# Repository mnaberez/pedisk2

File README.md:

# PEDISK II

This repository holds reverse engineering work on the
[PEDISK II](http://mikenaberezny.com/hardware/pet-cbm/microtech-pedisk-ii/) from CGRS Microtech,
a floppy disk controller for Commodore PET/CBM computers.

## Files

 - `rom_e800.bin` is a binary dump of the EPROM.

 - `rom_e800.asm` is a disassembly of it.

## Assemble

The `.asm` files can be assembled with the
[ACME](http://www.esw-heim.tu-clausthal.de/~marco/smorbrod/acme/)
assembler:

    $ acme -v1 --outfile test.bin pedisk2.asm

It should assemble a binary that is identical to the original.

## Credits

- Lee Davison did the initial disassembly of the ROM.
- Jim Oldfield provided the 5.25" PEDISK disks from which the DOS code was
  recovered.
- Mike Naberezny disassembled the 5.25" DOS code, adapted it for 8", and wrote
  the image tools.
- Steve Hirsch provided help and formatted 8" disks used for early testing.
- Josh Bensadon reverse engineered the original PCB and made the schematic.
- Steve Gray made the replica PCB layout and had boards manufactured.
- Mike Stein built the replica and provided help and input throughout.
- Bill Goble, the original designer of the PEDISK, found and donated the
  original manuals, schematics, source code, and master disks.

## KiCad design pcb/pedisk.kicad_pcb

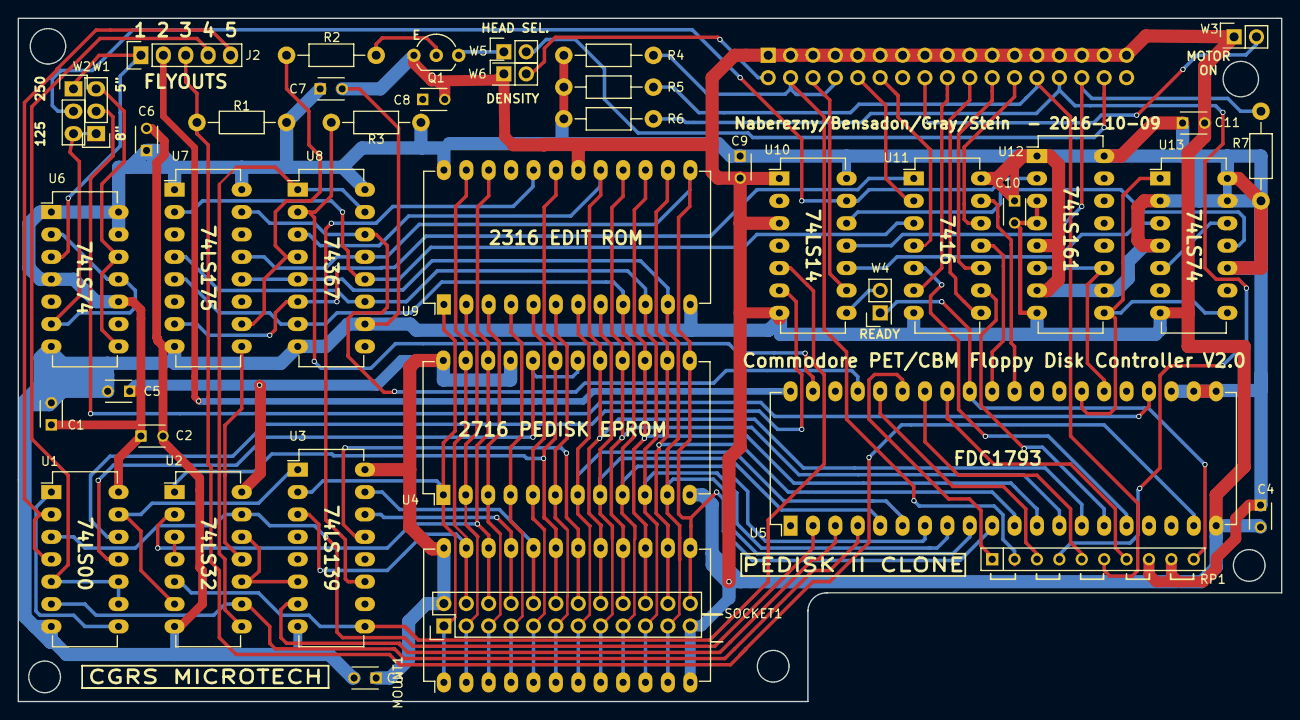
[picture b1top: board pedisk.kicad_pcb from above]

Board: 2 copper layers, 143.3 x 77.5 mm, 43 parts (1 on the bottom side), 82 nets.

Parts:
C1, C2, C3, C4, C5, C6, C7, C8, C9, C10, C11: C; C_Disc_D3_P2.5
J2: CONN_01X05; Pin_Header_Straight_1x05
MOUNT1: 2316; DIP-24_W15.24mm_LongPads
P1: CONN_02X17; IDC_Header_Straight_34pins
Q1: 2N2222; TO-92_Inline_Wide
R1, R2, R3, R7: 3.3K; Resistor_Horizontal_RM10mm
R4, R5, R6: 150ohm; Resistor_Horizontal_RM10mm
RP1: 4.7K; Resistor_Array_SIP9
SOCKET1: CONN_02X12; Pin_Header_Straight_2x12
U1: 74HC00; DIP-14_W7.62mm_LongPads
U2: 74LS32; DIP-14_W7.62mm_LongPads
U3: 74LS139; DIP-16_W7.62mm_LongPads
U4: 2716; DIP-24_W15.24mm_LongPads
U5: FD1793; DIP-40_W15.24mm_LongPads
U6, U13: 74LS74; DIP-14_W7.62mm_LongPads
U7: 74LS175; DIP-16_W7.62mm_LongPads
U8: 74LS367; DIP-16_W7.62mm_LongPads
U9: 2316; DIP-24_W15.24mm_LongPads
U10: 74HC14; DIP-14_W7.62mm_LongPads
U11: 74LS05; DIP-14_W7.62mm_LongPads
U12: 74LS161; DIP-16_W7.62mm_LongPads
W1: 8 5; Pin_Header_Straight_1x03
W2: 250 125; Pin_Header_Straight_1x03
W3, W4, W5, W6: CONN_02X01; Pin_Header_Straight_2x01

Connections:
5V: C1.1, C2.1, C3.1, C4.1, C5.1, C6.1, C7.1, C8.1, C9.1, C10.1, C11.1, MOUNT1.24, R1.2, R3.1, R4.1, R5.1, R6.1, R7.1, RP1.8, RP1.9, SOCKET1.2, U1.14, U2.14, U3.16, U4.21, U4.24, U5.21, U5.22, U5.23, U6.1, U6.4, U6.10, U6.13, U6.14, U7.1, U7.16, U8.16, U9.21, U9.24, U10.14, U11.14, U12.1, U12.5, U12.7, U12.10, U12.16, U13.2, U13.4, U13.10, U13.13, U13.14
12VOLTS: J2.2, U5.40
A0: MOUNT1.8, SOCKET1.15, U4.8, U5.5, U9.8
A1: MOUNT1.7, SOCKET1.13, U4.7, U5.6, U9.7
A2: MOUNT1.6, SOCKET1.11, U4.6, U9.6
A3: MOUNT1.5, SOCKET1.9, U4.5, U9.5
A4: MOUNT1.4, SOCKET1.7, U4.4, U9.4
A5: MOUNT1.3, SOCKET1.5, U4.3, U9.3
A6: MOUNT1.2, SOCKET1.3, U4.2, U9.2
A7: MOUNT1.1, SOCKET1.1, U3.2, U4.1, U9.1
A8: MOUNT1.23, SOCKET1.4, U3.3, U4.23, U9.23
A9: MOUNT1.22, SOCKET1.6, U2.2, U4.22, U9.22
A10: MOUNT1.19, SOCKET1.12, U2.1, U4.19, U9.19
A11: MOUNT1.21, SOCKET1.8, U3.14
CLK: U5.24, W1.2
CLOCK: J2.1, U6.3, W2.1
D0: MOUNT1.9, SOCKET1.17, U4.9, U5.7, U7.5, U8.7, U9.9
D1: MOUNT1.10, SOCKET1.19, U4.10, U5.8, U7.4, U8.11, U9.10
D2: MOUNT1.11, SOCKET1.21, U4.11, U5.9, U7.12, U8.5, U9.11
D3: MOUNT1.13, SOCKET1.24, U4.13, U5.10, U7.13, U8.13, U9.13
D4: MOUNT1.14, SOCKET1.22, U4.14, U5.11, U9.14
D5: MOUNT1.15, SOCKET1.20, U4.15, U5.12, U9.15
D6: MOUNT1.16, SOCKET1.18, U4.16, U5.13, U9.16
D7: MOUNT1.17, SOCKET1.16, U4.17, U5.14, U8.3, U9.17
DENSITY: P1.2, W6.2
DIRC: P1.18, U11.6
E: J2.5, U1.2, U1.4
EPROM_CS: U1.11, U4.18, U4.20
FDC_CS: U3.7, U5.3
FDC_RE: U1.6, U2.9, U5.4
FDC_WE: U1.3, U2.13, U5.2
GND: C1.2, C2.2, C3.2, C4.2, C5.2, C6.2, C7.2, C8.2, C9.2, C10.2, C11.2, MOUNT1.12, P1.1, P1.3, P1.5, P1.7, P1.9, P1.11, P1.13, P1.15, P1.17, P1.19, P1.21, P1.23, P1.25, P1.27, P1.29, P1.31, P1.33, Q1.1, SOCKET1.23, U1.7, U2.7, U3.8, U4.12, U5.20, U6.7, U7.8, U8.8, U8.10, U9.12, U9.18, U10.1, U10.3, U10.7, U11.7, U12.3, U12.4, U12.8, U13.7, W3.1, W6.1
HDSEL: P1.32, W5.2
INDEX: P1.4, P1.8, R4.2, RP1.2
INTRQ: R3.2, U5.39, U8.2
LATCH_READ: U2.8, U8.1, U8.15
LATCH_WRITE: U2.11, U7.9
MOTOR: P1.16, W3.2
unnamed: Q1.2, R2.2
unnamed: Q1.3, W5.1
unnamed: R2.1, U7.10, U8.4
unnamed: RP1.1, U5.35
unnamed: RP1.3, U5.36
unnamed: RP1.5, U5.34
unnamed: RP1.7, U5.33
unnamed: RP1.10, U5.32, W4.1
unnamed: U1.1, U1.8
unnamed: U1.12, U10.6
unnamed: U1.13, U2.6, U3.1
unnamed: U2.3, U2.4
unnamed: U2.10, U2.12, U3.6
unnamed: U6.2, U6.6, U6.11, W1.1, W2.3
unnamed: U6.8, U6.12, W1.3
unnamed: U2.5, U3.9, U10.5
unnamed: U10.8, W4.2
unnamed: U10.10, U13.3
unnamed: U10.12, U13.11
unnamed: U10.13, U12.2, W2.2
unnamed: U7.7, U8.6, U11.1
unnamed: U7.2, U8.12, U11.3
unnamed: U5.16, U11.5
unnamed: U5.15, U11.9
unnamed: U5.31, U11.11
unnamed: U5.30, U11.13
unnamed: U13.5, U13.12
R/~W: J2.4, U1.5, U1.9, U1.10
RAWREAD: U5.27, U12.9, U13.1, U13.8
RCLK: U5.26, U12.6, U12.11
RDATA: P1.30, R7.2, U10.11
READY: P1.6, U10.9
RESET: J2.3, R1.1, U5.19
ROM_CS: U3.11, U9.20
SEL1: P1.10, U11.2
SEL2: P1.12, U11.4
SOCKET_CS: MOUNT1.20, SOCKET1.10, U3.15
SOCKET_OE: MOUNT1.18, SOCKET1.14, U3.13
STEP: P1.20, U11.8
TRK00: P1.26, R5.2, RP1.6
WDAT: P1.22, U11.10
WGATE: P1.24, U11.12
WPROT: P1.28, R6.2, RP1.4
~DDEN: U5.37, U7.15, U8.14

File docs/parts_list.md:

Parts List
----------

| Reference      | Part               |
|----------------|--------------------|
| C1-11          | 0.1 uF             |
| J1             | 34-pin Header      |
| Q1             | 2N2222 (??)        |
| R1, R2, R3, R7 | 3.3 K              |
| R4, R5, R6     | 150 Ohm            |
| RN1            | 4.7 K              |
| U1             | 74LS00             |
| U2             | 74LS32             |
| U3             | 74LS139            |
| U4             | 2716               |
| U5             | WD1793             |
| U6             | 74LS74             |
| U7             | 74LS175            |
| U8             | 74367              |
| U9             | 901474-03          |
| U10            | 74LS14             |
| U11            | 7416               |
| U12            | 74LS161            |
| U13            | 74LS74             |
| W1, W2         | 3-pin Jumper Block |
| W3, W4, W5     | 2-pin Jumper Block |

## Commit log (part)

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2015-02-21 Fix disassembly of JSR $7818
2015-02-21 Add labels for menu commands
2015-02-21 Add label l_ead1 for $EAD1
2015-02-21 Replace $7FB1 with drive_sel_f
2015-02-21 Found filler area
2015-02-21 Add labels and comments to internal commands
2015-02-21 Add label try_extrnl_cmd for $7a47
2015-02-21 Found hex word input
2015-02-21 Found character input
2015-02-22 Replace LB8F6 with linget
2015-02-22 Remove unused equates
2015-02-22 Replace $7a47 with try_extrnl_cmd
2015-02-22 Use character literal for command "P"
2015-02-22 Remove unused equate
2015-02-22 Replace L7AD1 with input_device
2015-02-22 Use equates for filename and drive_sel_f
2015-02-22 Replace $7ee0 with buf_4
2015-02-22 Move original binaries to bin/
2015-02-22 Found pointers to dir_sector
2015-02-22 Use equates for track, sector, drive_sel
2015-02-22 Replace $26 with hex_save_a
2015-02-22 Replace $22/23 with dir_ptr
2015-02-22 Add equates for RAM locations, add comments to program flow
2015-02-22 Replace $ea2f with drive_selects
2015-02-22 Use equate for chrin
2015-02-22 Replace $e900 with latch
2015-02-23 Add note that BASIC shortcuts can be used
2015-02-23 Fix indentation
2015-02-23 Add comments to menu input
2015-02-23 Replace $7800 with dos_stop
2015-02-23 Replace $7fe0 with wedge_stack
2015-02-23 Found tokenized BASIC at $7d0c
2015-02-23 Found tokenized BASIC at $7a00
2015-02-23 Add error info for select_drive, seek_track, find_file, load_file
2015-02-24 Add comments to find_file and load_file error handling
2015-02-24 Add comments to load program and execute program
2015-02-24 Rename exec_file to exec_prog for consistency
2015-02-24 Found start and entry addresses
2015-02-24 Replace $11/12 with linnum
2015-02-24 Add comments with directory entry indexes
2015-02-24 Found routine that prints filename
2015-02-24 Rename dir_a/dir_b to old_dir/new_dir
2015-02-24 Fix description of used file entry count
2015-02-24 Add labels and comments to directory manipulation
2015-02-25 Add equate tmp_7f97 for $7f97
2015-02-25 Found file data buffer
2015-02-25 Found number of used entries and next open track/sector
2015-02-25 Found directory read and write
2015-02-25 Found start of file move
2015-02-25 Add equate tmp_7f9a for $7f9a
2015-02-25 Add comments to sector increment error handling
2015-02-25 Rename start_move_file to move_file_loop
2015-02-25 Add equate intflg for $08
2015-02-25 Found 16 byte buffer for directory entry
2015-02-25 Remove equate L0076
2015-02-25 Add comments to explain dir_entry offsets
2015-02-25 Rename l_ead1 to restart_dos
2015-02-26 Add description of disk error message
2015-02-26 Found possible sectors per track constant
2015-02-26 Found file exists error code
2015-02-26 Add note about drive selection in seek_track
2015-02-26 Found return values for wait_for_fdc and wait_fdc_status
2015-02-27 Add comments to directory initialization
2015-02-27 Fix description of drive select
2015-02-27 Start format program to bootstrap a PEDISK disk
2015-02-28 Formats a disk successfully
2015-02-28 Fix description of track seek
2015-02-28 Print "FORMAT TRACK" before each track, not after
2015-02-28 Write empty directory after format
2015-03-01 Add comments to kill_file
2015-03-01 Add comments to input_device, rename L7ADB to parse_drive
2015-03-01 Fix typo
2015-03-02 Found BASIC tokens in _dos_run
2015-03-02 Add note about unused bytes in directory header
2015-03-02 Rename L7DDB to wait_for_r_key
2015-03-02 Remove unused label L7CAE
2015-03-02 Found source and destination drives
2015-03-02 Found sector buffer at $7e00
2015-03-02 Found buffer used to store sectors during copy
2015-03-02 Found current track number during copy
2015-03-02 Remove unused label hit_r_key
2015-03-03 Replace $7b59 with L7B59
2015-03-06 Clarify that head load solenoid may not only be 8"
2015-03-06 Rename deselect to deselect_drive for parity with select_drive
2015-03-07 Found save routine
2015-03-09 Add note with file types that can be loaded
2015-03-12 Assemble format.asm on Travis
2015-03-13 Found "restore" command
2015-03-23 Found purpose of status check after write protect check
2015-03-28 Add TODO for offset $0b in directory entry
2015-04-03 Add troubleshooting note about double sided disks
2015-04-04 Add troubleshooting note about hard sectored disks
2015-04-05 Fix typo in string
2015-04-06 Found usage for !OPEN, !CLOSE, !PRINT, !INPUT Issue 2 of the PEDISK newsletter has a program listing that shows these commands in use.
2015-04-06 Found optional keywords that may follow !OPEN
2015-04-06 Found another possible BASIC token
2015-04-06 Use character literal for colon
2015-04-07 Found basics of record handling for !PRINT and !INPUT
2015-04-07 Found record count specifier
2015-04-08 Found unknown END mode of !OPEN
2015-04-08 Found strings
2015-04-08 Found error codes set in FC% variable
2015-04-08 Found error handler for sequential commands
2015-04-10 Found FC% error codes for !OPEN
2015-04-12 Found routine to get open file number
2015-04-12 Found error code for file not open
2015-04-12 Found error code for too many open files
2015-04-12 Found !OPEN logic for create new or open existing
2015-04-12 Add labels to !OPEN routines
2015-04-12 Rename L7B2F to file_num_to_xy
2015-04-13 Replace $7BE9 with label
2015-04-13 Found error code for position out of range
2015-04-14 Fix usage of POS keyword
2015-04-14 Found FC% error code for OK
2015-04-14 Rename L79F3 to sys_disk_err
2015-04-16 Rename L7BA6 to handle_filename
2015-04-16 Remove unused label
2015-04-16 Add labels for open_create branches
2015-04-18 Found filler bytes at $79f6
2015-04-20 Remove old TODO
2015-04-21 Remove old reference to buf_*
2015-04-22 Add note with L7931 callers
2015-04-23 Add description of input_filename
2015-04-25 Remove incorrect comment
2015-04-25 Rename l_ed38 to cli_rts
2015-04-26 Rename L7D7D to "done"
2015-04-26 Compact filler area
2015-05-08 Use sector_size constant
2015-05-11 Remove comment
2015-11-16 Add class for manipulating PEDISK image data
2015-11-16 Fix empty space fill byte
2015-11-16 Move format into Filesystem object
2015-11-16 Add tests for format
2015-11-16 Pad diskname to 8 bytes
2015-11-16 Add method to find next available track/sector
2015-11-16 Add properties to find free space
2015-11-16 Add method to write an LD file
2015-11-16 Fix missing entry address
2015-11-17 Add a script to make a boot disk
2015-11-17 Add description for format program
2015-11-17 Add bootstrap file generator
2015-11-17 Display code if error occurs
2015-11-17 Add banner to show format program version
2015-11-17 Rename 8" version of format to format8.asm
2015-11-17 Combine writes for track and sector
2015-11-17 Use ljust() to pad
2015-11-17 Move ljust() closer to writes
2015-11-17 Remove redundant range check
2015-11-17 Move reading track/sector above validations
2015-11-17 Combine redundant range tests
2015-11-17 Add method to list directory
2015-11-18 Fix seeking to next available entry
2015-11-18 Add test for read_dir()
2015-11-18 Move filename validation into DirectoryEntry
2015-11-19 Only check bounds after increment
2015-11-19 Fix reading directory entry, add tests
2015-11-19 Remove write_ld_file()
2015-11-20 Add ability to read disk name and rename disk
2015-11-20 Allow write_file() to overwrite entries of deleted files
2015-11-20 Count file entries instead of blindly incrementing count in header
2015-11-20 Add file_exists() to check for existence of file
2015-11-20 write_file() now raises if file already exists
2015-11-21 Fix disk conversion broken by changes in filesystem API
2015-11-21 Rewrite seek() to not use _incr()
2015-11-22 Fix disk conversion
2015-11-22 Print complete directory information
2015-11-22 Fix writing the largest possible file
2015-11-22 Fix reading the largest possible file
2015-11-22 Add tests for writing an empty file
2015-11-23 Allow read_file() to return partial data if dir is inconsistent
2015-11-23 Show and extract deleted files
2015-11-23 Fix write_file() overwriting a deleted file entry
2015-11-23 Copy all files during conversion, including deleted
2015-11-23 Add .gitignore file
2015-11-23 Add MTEST.LD file from a 5.25" disk
2015-11-23 Add initial disassembly of MTEST.LD
2015-11-23 Reindent at 4 spaces
2015-11-23 Add whitespace between subroutines
2015-11-23 Add labels for chrout routines
2015-11-23 Use character literals
2015-11-25 Preserve the unknown byte in the directory entry
2015-11-25 Move track/sector validation and counting to DiskImage
2015-11-25 Fix read_image() function using global
2015-11-25 Move modern_filename() into DirectoryEntry
2015-11-25 Rewrite script into functions
2015-11-26 Add read_data() to read data for a directory entry
2015-11-26 Get expected data size from entry, not filename
2015-11-26 Remove 5.25" disk assumptions in tests
2015-11-26 Refactor read_data() to use expected_data_size()
2015-11-27 Whitelist file types known to use the size field
2015-11-27 Ensure no more data than the sector count is returned
2015-11-27 Preserve unknown byte during conversion
2015-11-29 Bootstrap an entire disk by storing tracks in separate files
2015-11-29 Move assembly and image creation into functions
2015-11-29 Remove duplicate definition for UNUSED
2015-11-29 Add equates for RAM locations
2015-11-29 Shorten print_filename by using Y register
2015-11-29 Allow using device numbers other than 8
2015-11-29 Remove outdated bootstrap program
2015-11-29 Check for error after writing PEDISK track
2015-12-04 Fix ACME download link
2015-12-10 Search for free entry from bottom up
2015-12-10 Remove _seek_to_free_entry()
2016-04-12 Add schematic drawn by Josh Bensadon
2016-04-12 Add note that bit 3 is /DDEN
2016-04-13 Add connection list based on work by Mike Stein
2016-04-13 Add note about /DDEN
2016-04-13 Mark no-connects on PEDISK connector
2016-04-13 Add note for READY signal on FDD100-8
2016-04-15 Add standalone format program for 5.25"
2016-04-15 Found INTRQ on bit 7 of U8
2016-04-15 Use the same names as the schematic
2016-04-15 Fix part number of U3 (74139 should be 74LS139)
2016-04-16 Fix U12 pin 10 and add jumper W3
2016-04-16 Fix swapped U10/U11 designator on inverter
2016-04-22 Update schematic with changes from Josh Bensadon
2016-09-29 Build image files on Travis
2016-09-29 Build bootstrap image on Travis
2016-09-29 Allow making bootstrap image from any directory
2016-09-29 Move assembly sources to src/
2016-09-29 Use literals for printable chars
2016-09-29 Add comments to explain meaning of POKEs
2016-09-29 Move Initialization under BASIC Wedge section
2016-09-29 Fix 74LS175 part number
2016-09-30 Rename to avoid issues copying out of the image
2016-10-07 Print more granular status messages
2016-10-07 Clarify that image is a PEDISK image
2016-10-08 Use consistent style for labels
2016-10-08 Found track and sector storage
2016-10-09 Fix size of buffer at dir_entry
2016-10-10 Fix description of handle_filename
2016-10-10 Rename dos_stop to dos_monitor
2016-10-10 Add KiCad extensions to .gitattributes
2016-10-10 Added Kicad files for PCB
    This is an updated version of the PCB design with modified mounting,
    some components moved slightly, updated labelling and additional jumper.
2016-10-11 Add note to investigate "NEW LEN" without number
2016-10-11 Use literal for consistency
2016-10-11 Add constants for FC% error codes
2016-10-12 Fix syntax highlighting
2016-10-13 Be explicit instead of parsing filename
2016-10-13 Fix build
2016-10-16 Move historic build/compare script to tools/
2016-10-16 Fix encoding for Python 3 compat
2016-10-16 Fix build on Python 2
2016-10-16 Credit all contributors
2016-10-16 Note possible bit flip
2016-10-16 Ignore __pycache__/
2016-10-17 Use splitext instead of replace
2016-10-17 PEDISK program files must not have CBM style load address
2016-10-17 Credit Steve Hirsch
2016-10-22 Tester program in CBM BASIC 4
    tester.txt is plaintext listing of TESTER.PRG
2016-10-23 tester.bas - fix range check for print
    change "9" to ":"
2016-11-04 Improve description of LEN parsing
2016-12-07 Add Bill Goble to the credits
2016-12-10 Add support for 5.25" single density image files
2016-12-10 Rename f_unknown_2b to f_out_of_space
2016-12-11 Add support for 40 track FM disk images
2021-01-03 Add workflow for GitHub Actions
2021-01-03 Begin support for PEDISK I images
